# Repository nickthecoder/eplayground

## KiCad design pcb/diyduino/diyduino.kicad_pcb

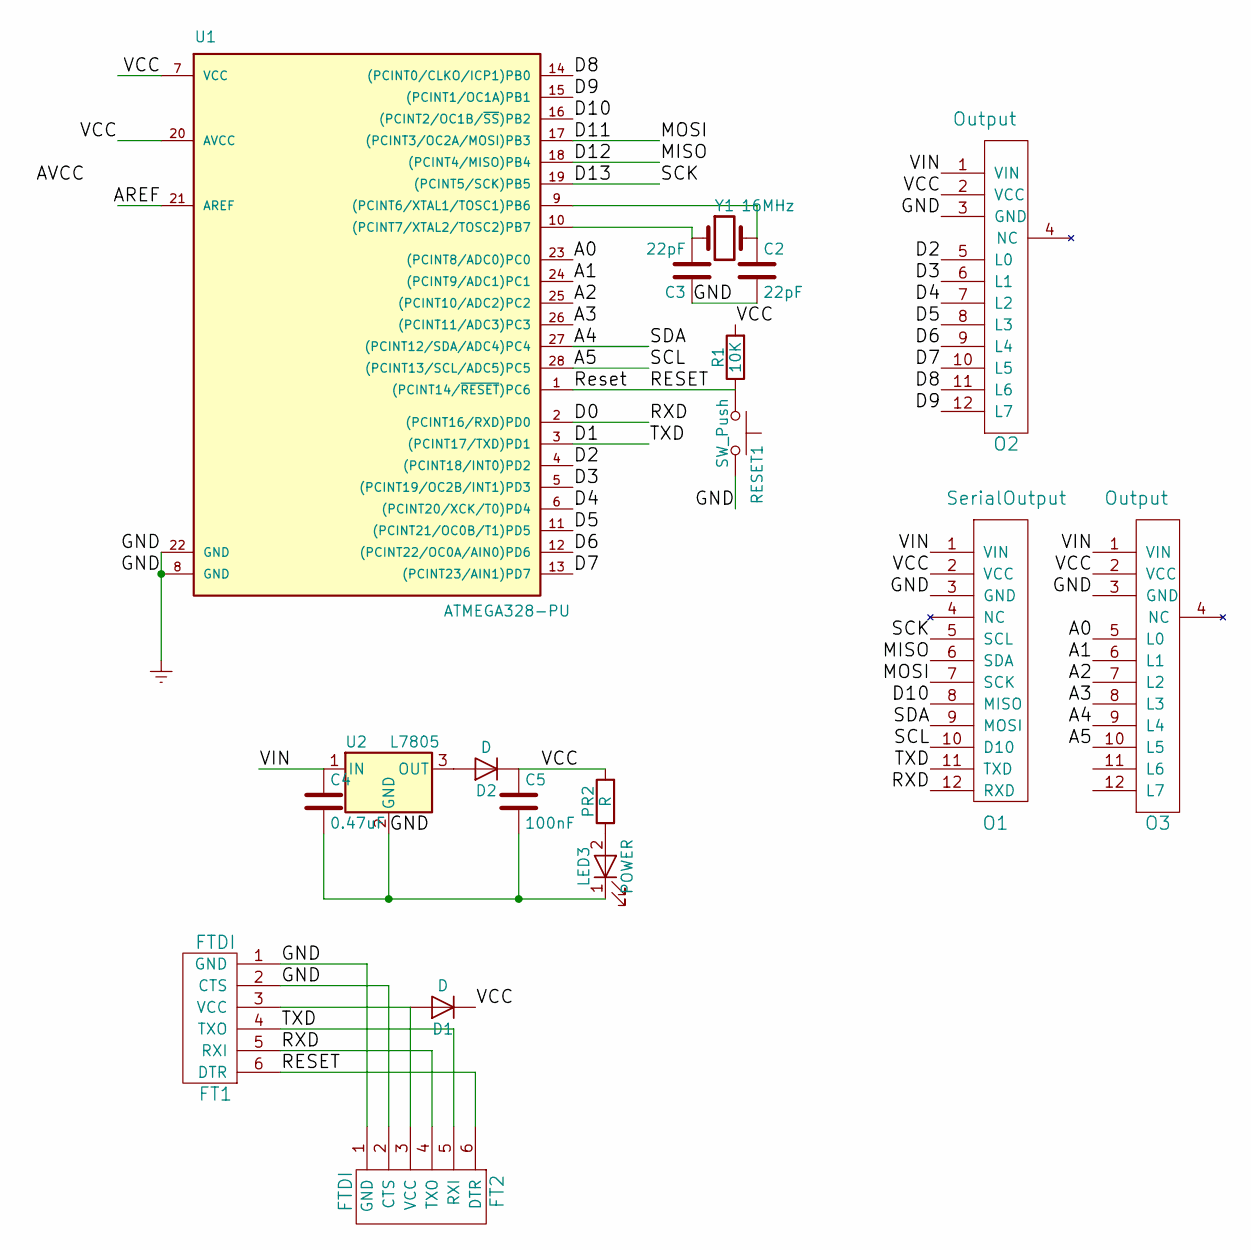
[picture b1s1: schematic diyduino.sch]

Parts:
C2, C3: 22pF; C_Disc_D3.0mm_W1.6mm_P2.50mm
C4: 0.47uF; CP_Radial_D6.3mm_P2.50mm
C5: 100nF; CP_Radial_D6.3mm_P2.50mm
D1, D2: D; D_T-1_P5.08mm_Horizontal
FT1, FT2: FTDI; Pin_Header_Straight_1x06_Pitch2.54mm
LED3: POWER; LED_Rectangular_W3.0mm_H2.0mm
O1: SerialOutput; Socket_Strip_Straight_1x12_Pitch2.54mm
O2, O3: Output; Socket_Strip_Straight_1x12_Pitch2.54mm
PR2: R; R_Axial_DIN0204_L3.6mm_D1.6mm_P7.62mm_Horizontal
R1: 10K; R_Axial_DIN0204_L3.6mm_D1.6mm_P7.62mm_Horizontal
RESET1: SW_Push; SW_PUSH_6mm
U1: ATMEGA328-PU; DIP-28_W7.62mm
U2: L7805; TO-220
Y1: 16MHz; Resonator-2pin_w6.0mm_h3.0mm

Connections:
/A0: O3.5 (L0), U1.23 ((PCINT8/ADC0)PC0)
/A1: O3.6 (L1), U1.24 ((PCINT9/ADC1)PC1)
/A2: O3.7 (L2), U1.25 ((PCINT10/ADC2)PC2)
/A3: O3.8 (L3), U1.26 ((PCINT11/ADC3)PC3)
/A4: O1.9 (MOSI), O3.9 (L4), U1.27 ((PCINT12/SDA/ADC4)PC4)
/A5: O1.10 (D10), O3.10 (L5), U1.28 ((PCINT13/SCL/ADC5)PC5)
/D0: FT1.5 (RXI), FT2.4 (TXO), O1.12 (RXD), U1.2 ((PCINT16/RXD)PD0)
/D1: FT1.4 (TXO), FT2.5 (RXI), O1.11 (TXD), U1.3 ((PCINT17/TXD)PD1)
/D2: O2.5 (L0), U1.4 ((PCINT18/INT0)PD2)
/D3: O2.6 (L1), U1.5 ((PCINT19/OC2B/INT1)PD3)
/D4: O2.7 (L2), U1.6 ((PCINT20/XCK/T0)PD4)
/D5: O2.8 (L3), U1.11 ((PCINT21/OC0B/T1)PD5)
/D6: O2.9 (L4), U1.12 ((PCINT22/OC0A/AIN0)PD6)
/D7: O2.10 (L5), U1.13 ((PCINT23/AIN1)PD7)
/D8: O2.11 (L6), U1.14 ((PCINT0/CLKO/ICP1)PB0)
/D9: O2.12 (L7), U1.15 ((PCINT1/OC1A)PB1)
/D10: O1.8 (MISO), U1.16 ((PCINT2/OC1B/~SS~)PB2)
/D11: O1.7 (SCK), U1.17 ((PCINT3/OC2A/MOSI)PB3)
/D12: O1.6 (SDA), U1.18 ((PCINT4/MISO)PB4)
/D13: O1.5 (SCL), U1.19 ((PCINT5/SCK)PB5)
/RESET: FT1.6 (DTR), FT2.6 (DTR), R1.1, RESET1.1, U1.1 ((PCINT14/~RESET~)PC6)
/VCC: C5.1, D1.1 (K), D2.1 (K), O1.2 (VCC), O2.2 (VCC), O3.2 (VCC), PR2.2, R1.2, U1.7 (VCC), U1.20 (AVCC)
/VIN: C4.1, O1.1 (VIN), O2.1 (VIN), O3.1 (VIN), U2.1 (IN)
Earth: C2.2, C3.1, C4.2, C5.2, FT1.1 (GND), FT1.2 (CTS), FT2.1 (GND), FT2.2 (CTS), LED3.1 (K), O1.3 (GND), O2.3 (GND), O3.3 (GND), RESET1.2, U1.8 (GND), U1.22 (GND), U2.2 (GND)
unnamed: C2.1, U1.9 ((PCINT6/XTAL1/TOSC1)PB6), Y1.2
unnamed: C3.2, U1.10 ((PCINT7/XTAL2/TOSC2)PB7), Y1.1
unnamed: D1.2 (A), FT1.3 (VCC), FT2.3 (VCC)
unnamed: D2.2 (A), U2.3 (OUT)
unnamed: LED3.2 (A), PR2.1

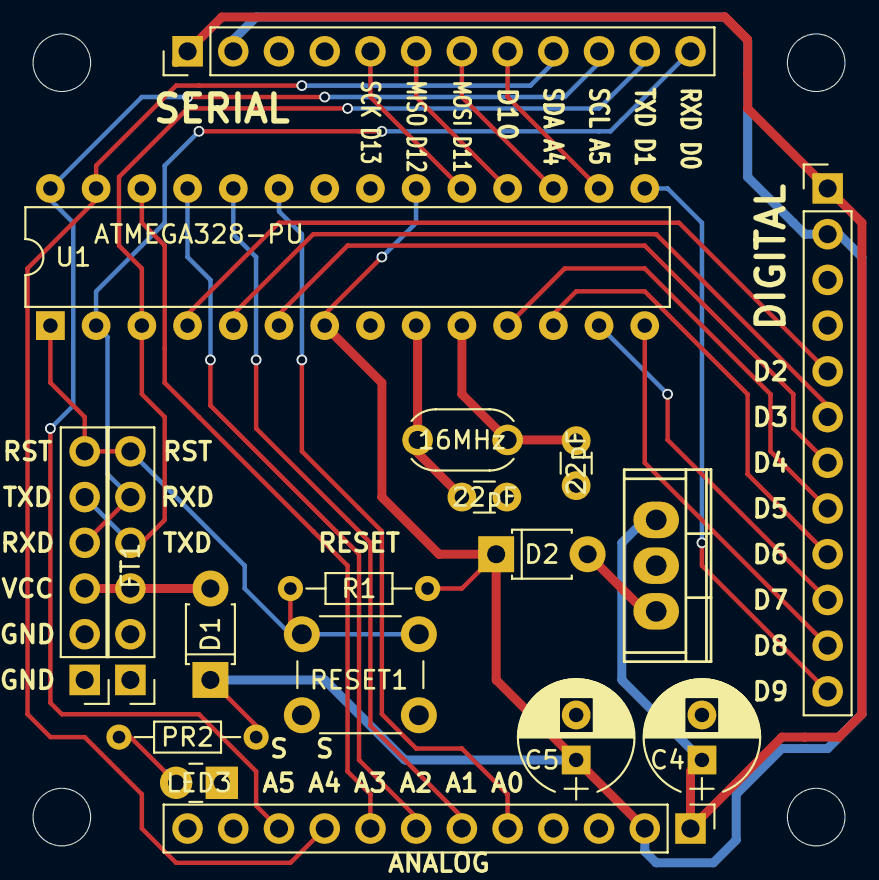
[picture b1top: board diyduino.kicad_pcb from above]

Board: 2 copper layers, 20 parts (0 on the bottom side), 29 nets.

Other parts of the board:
X: M3; MountingHole_3.2mm_M3
X#2: M3; MountingHole_3.2mm_M3

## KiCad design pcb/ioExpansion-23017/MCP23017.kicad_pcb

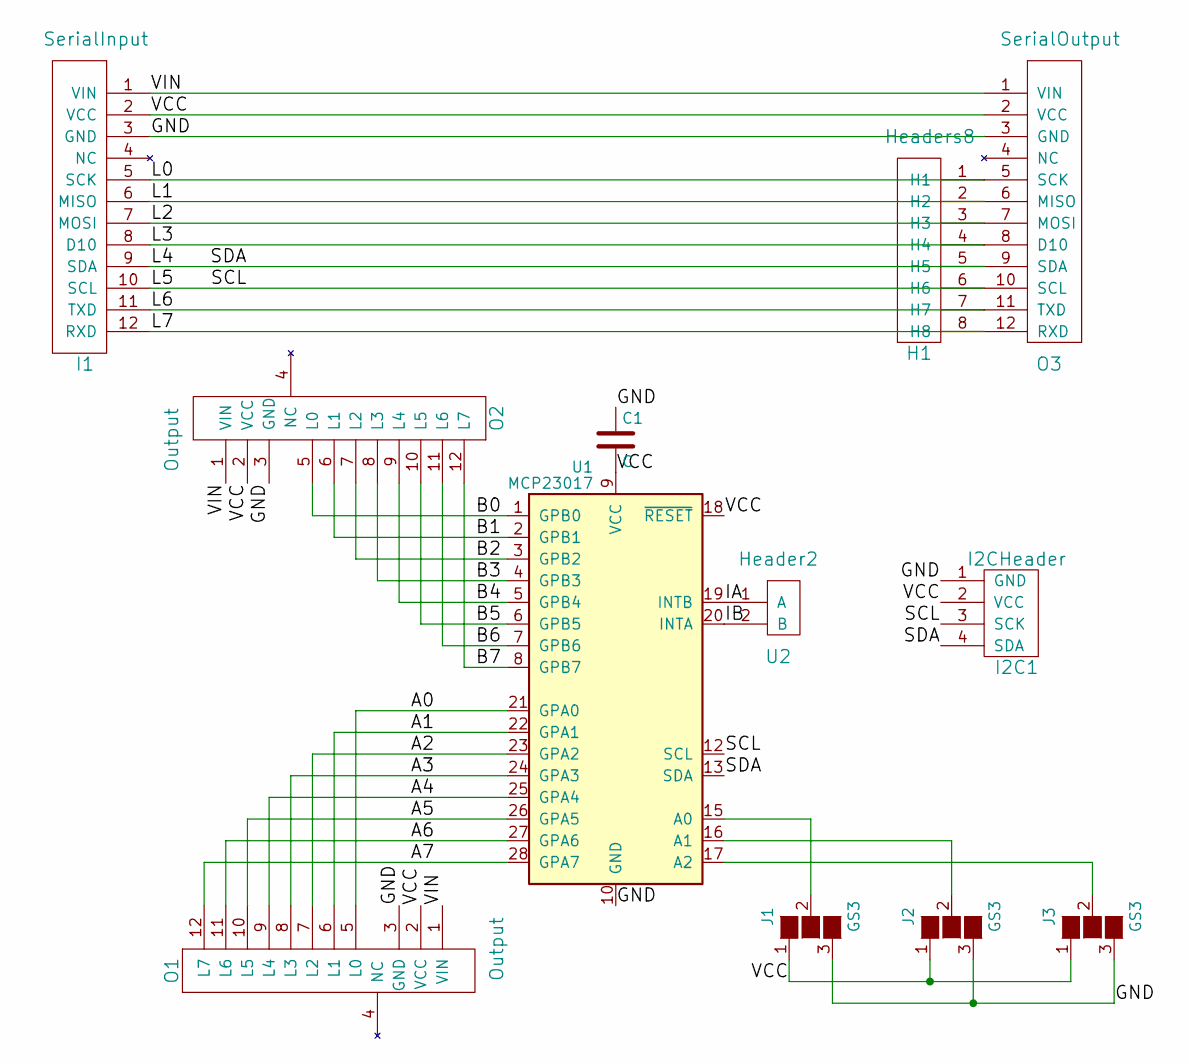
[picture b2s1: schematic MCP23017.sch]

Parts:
C1: C; C_Disc_D3.8mm_W2.6mm_P2.50mm
H1: Headers8; Pin_Header_Straight_1x08_Pitch2.54mm
I1: SerialInput; Socket_Strip_Straight_1x12_Pitch2.54mm
I2C1: I2CHeader; Pin_Header_Straight_1x04_Pitch2.54mm
J1, J2, J3: GS3
O1, O2: Output; Socket_Strip_Straight_1x12_Pitch2.54mm
O3: SerialOutput; Socket_Strip_Straight_1x12_Pitch2.54mm
U1: MCP23017; DIP-28_W7.62mm
U2: Header2; Pin_Header_Straight_1x02_Pitch2.54mm

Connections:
/A0: O1.5 (L0), U1.21 (GPA0)
/A1: O1.6 (L1), U1.22 (GPA1)
/A2: O1.7 (L2), U1.23 (GPA2)
/A3: O1.8 (L3), U1.24 (GPA3)
/A4: O1.9 (L4), U1.25 (GPA4)
/A5: O1.10 (L5), U1.26 (GPA5)
/A6: O1.11 (L6), U1.27 (GPA6)
/A7: O1.12 (L7), U1.28 (GPA7)
/B0: O2.5 (L0), U1.1 (GPB0)
/B1: O2.6 (L1), U1.2 (GPB1)
/B2: O2.7 (L2), U1.3 (GPB2)
/B3: O2.8 (L3), U1.4 (GPB3)
/B4: O2.9 (L4), U1.5 (GPB4)
/B5: O2.10 (L5), U1.6 (GPB5)
/B6: O2.11 (L6), U1.7 (GPB6)
/B7: O2.12 (L7), U1.8 (GPB7)
/GND: C1.1, I1.3 (GND), I2C1.1 (GND), J1.3 (G3), J2.3 (G3), J3.3 (G3), O1.3 (GND), O2.3 (GND), O3.3 (GND), U1.10 (GND)
/IA: U1.19 (INTB), U2.1 (A)
/IB: U1.20 (INTA), U2.2 (B)
/L0: H1.1 (H1), I1.5 (SCK), O3.5 (SCK)
/L1: H1.2 (H2), I1.6 (MISO), O3.6 (MISO)
/L2: H1.3 (H3), I1.7 (MOSI), O3.7 (MOSI)
/L3: H1.4 (H4), I1.8 (D10), O3.8 (D10)
/L4: H1.5 (H5), I1.9 (SDA), I2C1.4 (SDA), O3.9 (SDA), U1.13 (SDA)
/L5: H1.6 (H6), I1.10 (SCL), I2C1.3 (SCK), O3.10 (SCL), U1.12 (SCL)
/L6: H1.7 (H7), I1.11 (TXD), O3.11 (TXD)
/L7: H1.8 (H8), I1.12 (RXD), O3.12 (RXD)
/VCC: C1.2, I1.2 (VCC), I2C1.2 (VCC), J1.1 (G1), J2.1 (G1), J3.1 (G1), O1.2 (VCC), O2.2 (VCC), O3.2 (VCC), U1.9 (VCC), U1.18 (~RESET)
/VIN: I1.1 (VIN), O1.1 (VIN), O2.1 (VIN), O3.1 (VIN)
unnamed: J1.2 (G2), U1.15 (A0)
unnamed: J2.2 (G2), U1.16 (A1)
unnamed: J3.2 (G2), U1.17 (A2)

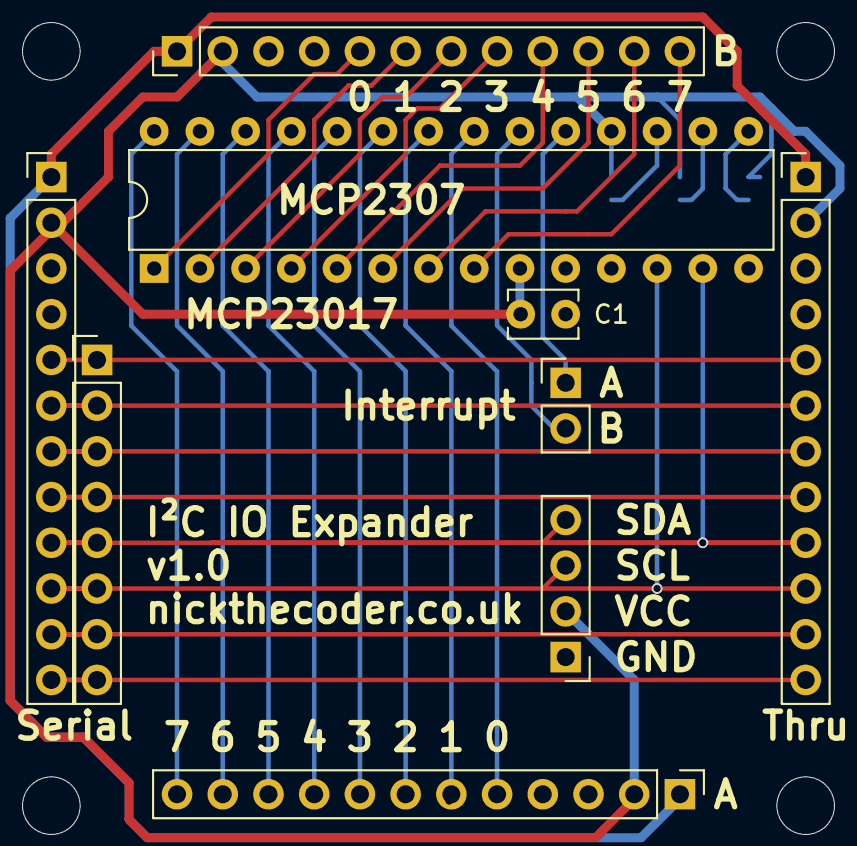
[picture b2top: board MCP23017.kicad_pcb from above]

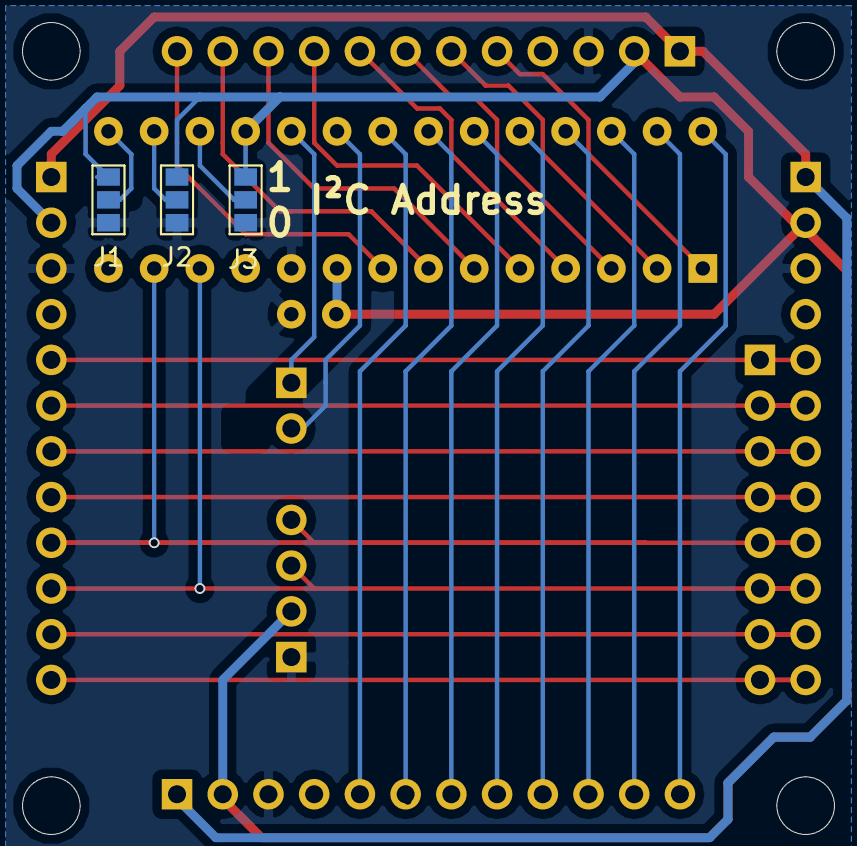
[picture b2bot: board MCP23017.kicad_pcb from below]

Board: 2 copper layers, 14 parts (3 on the bottom side), 32 nets.

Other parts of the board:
M3, M3#2: MountingHole_3.2mm_M3

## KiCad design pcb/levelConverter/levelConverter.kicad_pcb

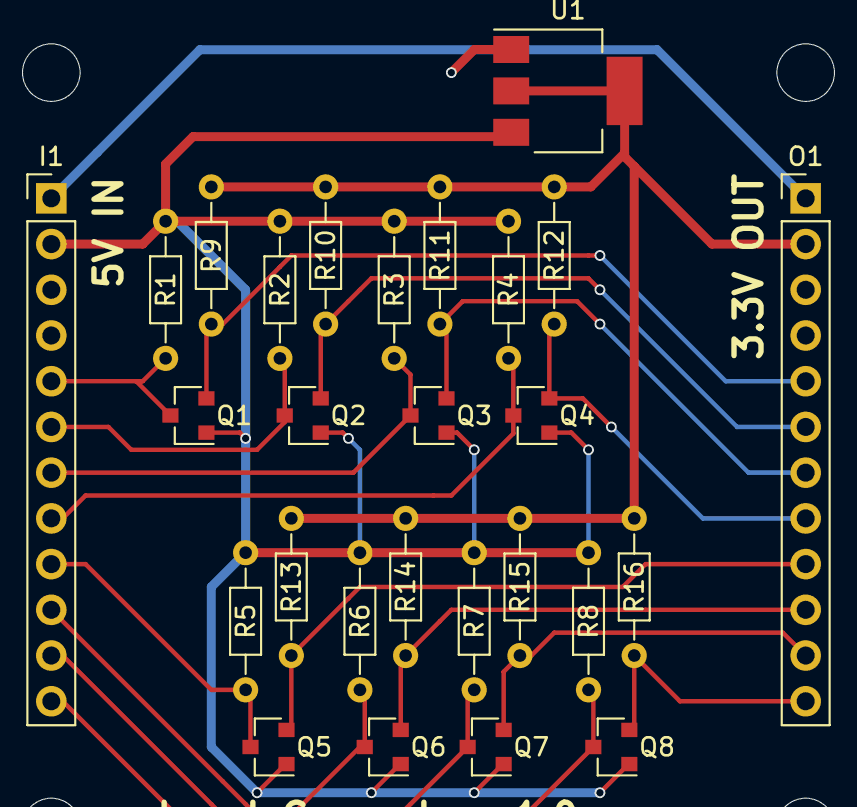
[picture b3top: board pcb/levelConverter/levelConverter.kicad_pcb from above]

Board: 2 copper layers, 29 parts (0 on the bottom side), 20 nets.

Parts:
I1: Input; Pin_Header_Straight_1x12_Pitch2.54mm
M3, M3#2: MountingHole_3.2mm_M3
O1: Output; Socket_Strip_Straight_1x12_Pitch2.54mm
Q1, Q2, Q3, Q4, Q5, Q6, Q7, Q8: BSS138; SOT-23
R1, R2, R3, R4, R5, R6, R7, R8, R9, R10, R11, R12, R13, R14, R15, R16: R; R_Axial_DIN0204_L3.6mm_D1.6mm_P7.62mm_Horizontal
U1: AP1117-33; SOT-223-3Lead_TabPin2

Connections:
/3v3: O1.2, R9.1, R10.1, R11.1, R12.1, R13.1, R14.1, R15.1, R16.1, U1.2
/5V: I1.2, Q1.1, Q2.1, Q3.1, Q4.1, Q5.1, Q6.1, Q7.1, Q8.1, R1.2, R2.1, R3.1, R4.1, R5.1, R6.1, R7.1, R8.1, U1.3
/L0: I1.5, Q1.3, R1.1
/L1: I1.6, Q2.3, R2.2
/L2: I1.7, Q3.3, R3.2
/L3: I1.8, Q4.3, R4.2
/L4: I1.9, Q5.3, R5.2
/L5: I1.10, Q6.3, R6.2
/L6: I1.11, Q7.3, R7.2
/L7: I1.12, Q8.3, R8.2
/VIN: I1.1, O1.1
Earth: I1.3, O1.3, U1.1
unnamed: O1.5, Q1.2, R9.2
unnamed: O1.6, Q2.2, R10.2
unnamed: O1.7, Q3.2, R11.2
unnamed: O1.8, Q4.2, R12.2
unnamed: O1.9, Q5.2, R13.2
unnamed: O1.10, Q6.2, R14.2
unnamed: O1.11, Q7.2, R15.2
unnamed: O1.12, Q8.2, R16.2

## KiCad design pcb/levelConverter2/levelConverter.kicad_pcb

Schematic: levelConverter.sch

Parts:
H1: Data; Pin_Header_Straight_1x08_Pitch2.54mm
H2: GND; Pin_Header_Straight_1x08_Pitch2.54mm
H3: VCC; Pin_Header_Straight_1x08_Pitch2.54mm
I1, I2: Input; Pin_Header_Straight_1x12_Pitch2.54mm
J1, J3: S; Pin_Header_Straight_1x01_Pitch2.54mm
J2, J4: Term; TerminalBlock_Pheonix_MPT-2.54mm_3pol
O1, O2: Output; Socket_Strip_Straight_1x12_Pitch2.54mm
Q1, Q2, Q3, Q4, Q5, Q6, Q7, Q8: BSS138; SOT-23
RN1, RN2: R_Network08; R_Array_SIP9
U1: AP1117-33; SOT-223-3Lead_TabPin2

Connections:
/3v3: O1.2 (VCC), RN1.1 (common), U1.2 (VO)
/5V: I1.2 (VCC), Q1.1 (G), Q2.1 (G), Q3.1 (G), Q4.1 (G), Q5.1 (G), Q6.1 (G), Q7.1 (G), Q8.1 (G), RN2.1 (common), U1.3 (VI)
/L0: I1.5 (L0), Q1.3 (D), RN2.2 (R1)
/L1: I1.6 (L1), Q2.3 (D), RN2.3 (R2)
/L2: I1.7 (L2), Q3.3 (D), RN2.4 (R3)
/L3: I1.8 (L3), Q4.3 (D), RN2.5 (R4)
/L4: I1.9 (L4), Q5.3 (D), RN2.6 (R5)
/L5: I1.10 (L5), Q6.3 (D), RN2.7 (R6)
/L6: I1.11 (L6), Q7.3 (D), RN2.8 (R7)
/L7: I1.12 (L7), Q8.3 (D), RN2.9 (R8)
/VIN: I1.1 (VIN), O1.1 (VIN)
Earth: H2.1 (H1), H2.2 (H2), H2.3 (H3), H2.4 (H4), H2.5 (H5), H2.6 (H6), H2.7 (H7), H2.8 (H8), I1.3 (GND), I2.3 (GND), J2.1, J4.1, O1.3 (GND), O2.3 (GND), U1.1 (GND)
unnamed: H1.1 (H1), I2.5 (L0), O2.5 (L0)
unnamed: H1.2 (H2), I2.6 (L1), O2.6 (L1)
unnamed: H1.3 (H3), I2.7 (L2), O2.7 (L2)
unnamed: H1.4 (H4), I2.8 (L3), O2.8 (L3)
unnamed: H1.5 (H5), I2.9 (L4), O2.9 (L4)
unnamed: H1.6 (H6), I2.10 (L5), O2.10 (L5)
unnamed: H1.7 (H7), I2.11 (L6), O2.11 (L6)
unnamed: H1.8 (H8), I2.12 (L7), O2.12 (L7)
unnamed: H3.1 (H1), H3.2 (H2), H3.3 (H3), H3.4 (H4), H3.5 (H5), H3.6 (H6), H3.7 (H7), H3.8 (H8), I2.2 (VCC), J2.2, J4.2, O2.2 (VCC)
unnamed: I2.1 (VIN), O2.1 (VIN)
unnamed: J1.1, J2.3
unnamed: J3.1, J4.3
unnamed: O1.5 (L0), Q1.2 (S), RN1.2 (R1)
unnamed: O1.6 (L1), Q2.2 (S), RN1.3 (R2)
unnamed: O1.7 (L2), Q3.2 (S), RN1.4 (R3)
unnamed: O1.8 (L3), Q4.2 (S), RN1.5 (R4)
unnamed: O1.9 (L4), Q5.2 (S), RN1.6 (R5)
unnamed: O1.10 (L5), Q6.2 (S), RN1.7 (R6)
unnamed: O1.11 (L6), Q7.2 (S), RN1.8 (R7)
unnamed: O1.12 (L7), Q8.2 (S), RN1.9 (R8)

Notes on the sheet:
https://learn.sparkfun.com/tutorials/bi-directional-logic-level-converter-hookup-guide
Level Converer
Triple Header
Option for one triple using screw terminal

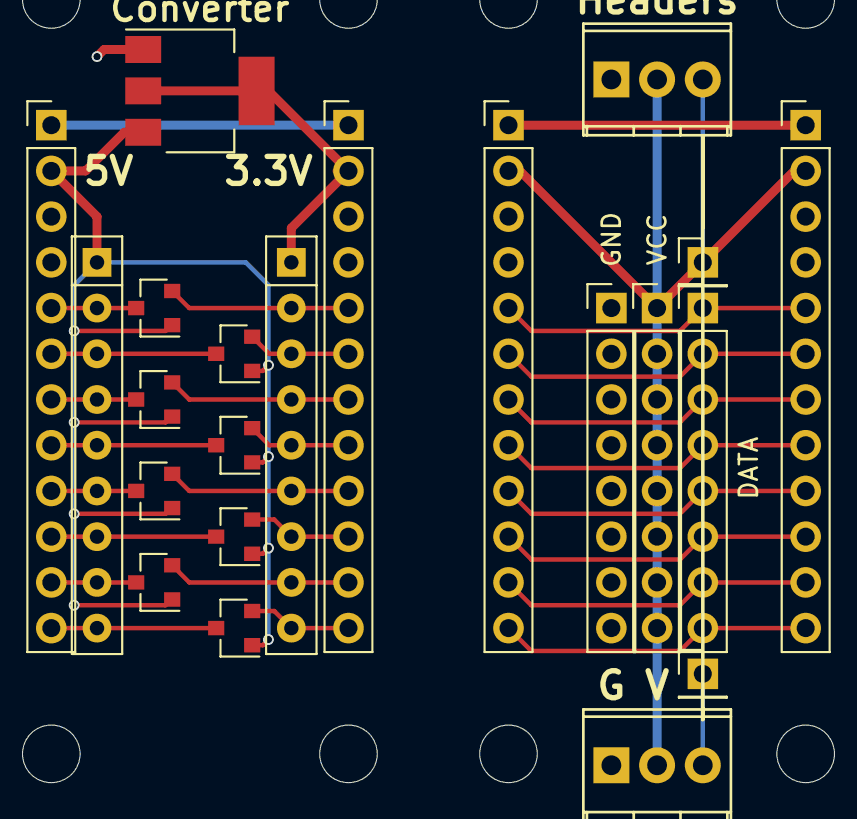
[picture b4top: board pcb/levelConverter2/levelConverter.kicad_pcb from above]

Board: 2 copper layers, 26 parts (0 on the bottom side), 32 nets.

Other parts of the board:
M3, M3#2, M3#3, M3#4: MountingHole_3.2mm_M3

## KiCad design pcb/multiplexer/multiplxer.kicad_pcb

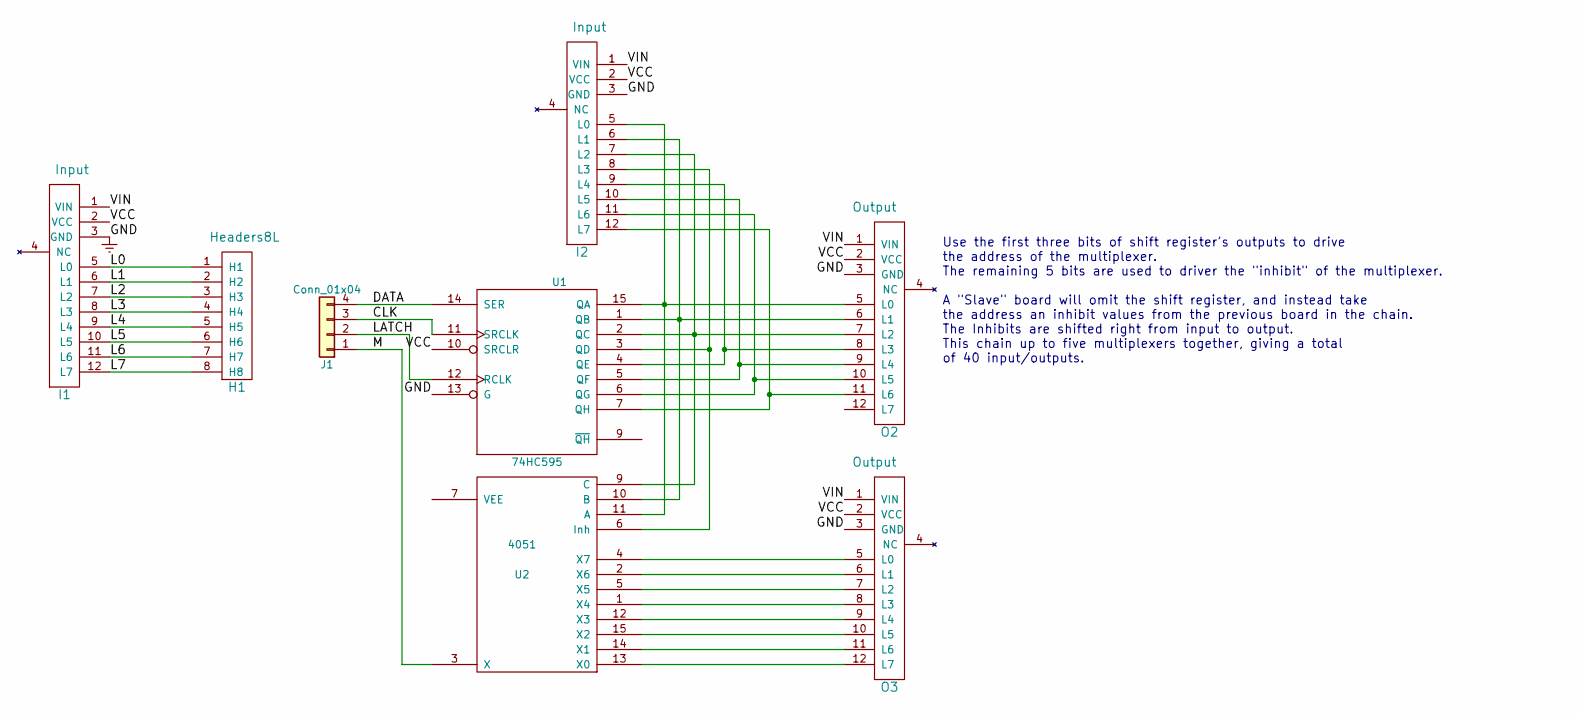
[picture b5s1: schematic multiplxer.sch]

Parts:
H1: Headers8L; Pin_Header_Straight_1x08_Pitch2.54mm
I1, I2: Input; Pin_Header_Straight_1x12_Pitch2.54mm
J1: Conn_01x04; Pin_Header_Straight_1x04_Pitch2.54mm
O2, O3: Output; Socket_Strip_Straight_1x12_Pitch2.54mm
U1: 74HC595; DIP-16_W7.62mm
U2: 4051; DIP-16_W7.62mm

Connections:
/CLK: J1.3, U1.11 (SRCLK)
/DATA: J1.4, U1.14 (SER)
/L0: H1.1 (H1), I1.5 (L0)
/L1: H1.2 (H2), I1.6 (L1)
/L2: H1.3 (H3), I1.7 (L2)
/L3: H1.4 (H4), I1.8 (L3)
/L4: H1.5 (H5), I1.9 (L4)
/L5: H1.6 (H6), I1.10 (L5)
/L6: H1.7 (H7), I1.11 (L6)
/L7: H1.8 (H8), I1.12 (L7)
/LATCH: J1.2, U1.12 (RCLK)
/M: J1.1, U2.3 (X)
/VIN: I1.1 (VIN), I2.1 (VIN), O2.1 (VIN), O3.1 (VIN)
Earth: I1.3 (GND), I2.3 (GND), O2.3 (GND), O3.3 (GND), U1.8 (GND), U1.13 (G)
unnamed: I2.5 (L0), O2.5 (L0), U1.15 (QA), U2.11 (A)
unnamed: I2.6 (L1), O2.6 (L1), U1.1 (QB), U2.10 (B)
unnamed: I2.7 (L2), O2.7 (L2), U1.2 (QC), U2.9 (C)
unnamed: I2.8 (L3), U1.3 (QD), U2.6 (Inh)
unnamed: I2.9 (L4), O2.8 (L3), U1.4 (QE)
unnamed: I2.10 (L5), O2.9 (L4), U1.5 (QF)
unnamed: I2.11 (L6), O2.10 (L5), U1.6 (QG)
unnamed: I2.12 (L7), O2.11 (L6), U1.7 (QH)
unnamed: O3.5 (L0), U2.4 (X7)
unnamed: O3.6 (L1), U2.2 (X6)
unnamed: O3.7 (L2), U2.5 (X5)
unnamed: O3.8 (L3), U2.1 (X4)
unnamed: O3.9 (L4), U2.12 (X3)
unnamed: O3.10 (L5), U2.15 (X2)
unnamed: O3.11 (L6), U2.14 (X1)
unnamed: O3.12 (L7), U2.13 (X0)
VCC: I1.2 (VCC), I2.2 (VCC), O2.2 (VCC), O3.2 (VCC), U1.10 (SRCLR), U1.16 (VCC)

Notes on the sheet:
Use the first three bits of shift register's outputs to drive the address of the multiplexer. The remaining 5 bits are used to driver the "inhibit" of the multiplexer. A "Slave" board will omit the shift register, and instead take the address an inhibit values from the previous board in the chain. 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

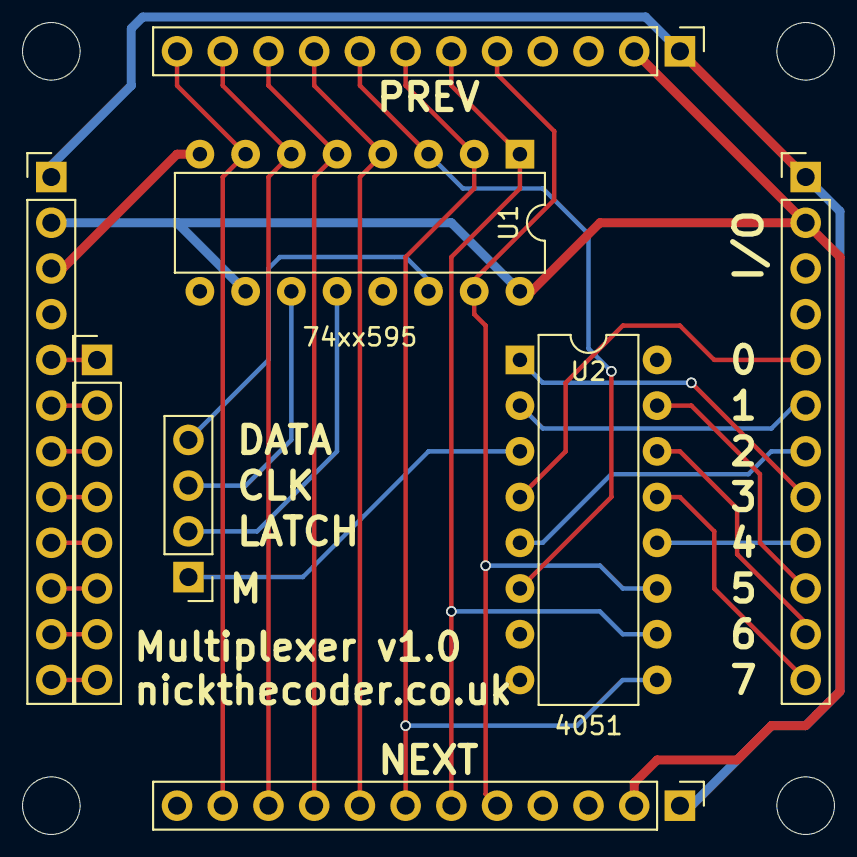
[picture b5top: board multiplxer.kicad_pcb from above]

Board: 2 copper layers, 10 parts (0 on the bottom side), 31 nets.

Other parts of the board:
M3, M3#2: MountingHole_3.2mm_M3

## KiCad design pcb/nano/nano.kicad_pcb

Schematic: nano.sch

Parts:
J2: Header2; Pin_Header_Straight_1x15_Pitch2.54mm
J3: Header1; Pin_Header_Straight_1x15_Pitch2.54mm
O1: SerialOutput; Socket_Strip_Straight_1x12_Pitch2.54mm
O2, O3: Output; Socket_Strip_Straight_1x12_Pitch2.54mm
XA1: Arduino_Nano_Socket; Arduino_Nano

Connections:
/3V3: J2.14, XA1.3V3 (3.3V)
/A0: J2.12, O3.12 (L7), XA1.A0
/A1: J2.11, O3.11 (L6), XA1.A1
/A2: J2.10, O3.10 (L5), XA1.A2
/A3: J2.9, O3.9 (L4), XA1.A3
/A4: J2.8, O1.9 (SDA), O3.8 (L3), XA1.A4 (A4_SDA)
/A5: J2.7, O1.10 (SCL), O3.7 (L2), XA1.A5 (A5_SCL)
/A6: J2.6, O3.6 (L1), XA1.A6
/A7: J2.5, O3.5 (L0), XA1.A7
/AREF: J2.13, XA1.AREF
/D0: J3.2, O1.12 (RXD), XA1.D0 (D0_RX0)
/D1: J3.1, O1.11 (TXD), XA1.D1 (D1_TX0)
/D2: J3.5, O2.5 (L0), XA1.D2 (D2_INT0)
/D3: J3.6, O2.6 (L1), XA1.D3 (D3_INT1)
/D4: J3.7, O2.7 (L2), XA1.D4
/D5: J3.8, O2.8 (L3), XA1.D5
/D6: J3.9, O2.9 (L4), XA1.D6
/D7: J3.10, O2.10 (L5), XA1.D7
/D8: J3.11, O2.11 (L6), XA1.D8
/D9: J3.12, O2.12 (L7), XA1.D9
/D10: J3.13, O1.8 (D10), XA1.D10 (D10_CS)
/D11: J3.14, O1.7 (MOSI), XA1.D11 (D11_MOSI)
/D12: J3.15, O1.6 (MISO), XA1.D12 (D12_MISO)
/D13: J2.15, O1.5 (SCK), XA1.D13 (D13_SCK)
/GND: J2.2, J3.4, O1.3 (GND), O2.3 (GND), O3.3 (GND), XA1.GND1 (GND), XA1.GND2 (GND)
/Reset1: J3.3, XA1.RST1 (RESET)
/Reset2: J2.3, XA1.RST2 (RESET)
/VCC: J2.4, O1.2 (VCC), O2.2 (VCC), O3.2 (VCC), XA1.5V
/VIN: J2.1, O1.1 (VIN), O2.1 (VIN), O3.1 (VIN), XA1.VIN

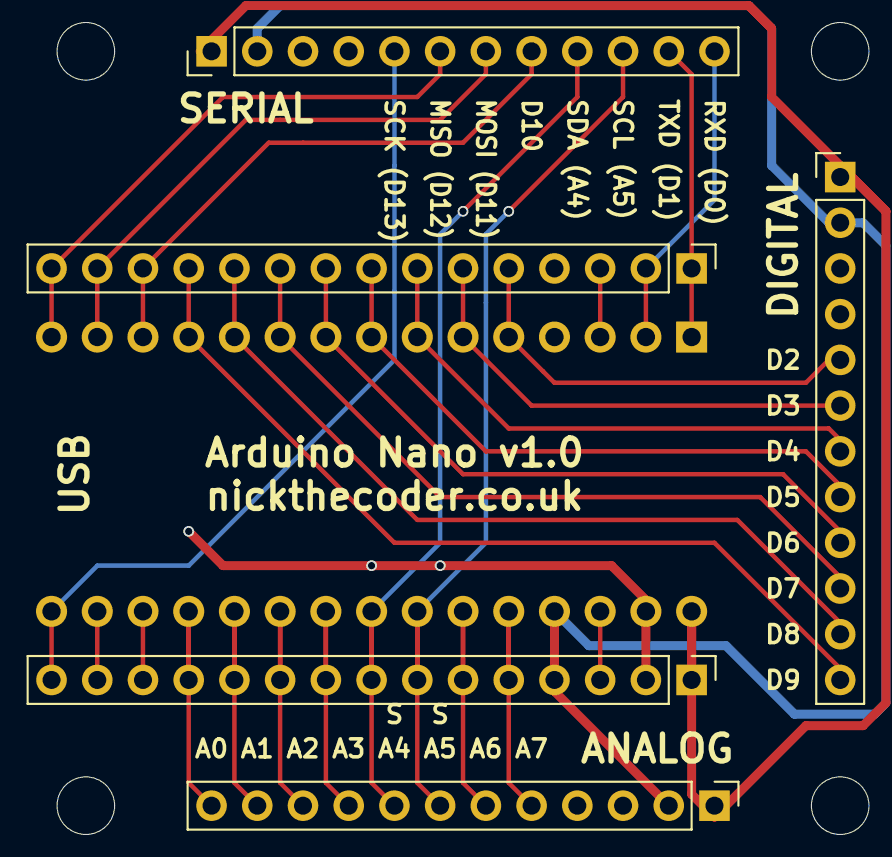
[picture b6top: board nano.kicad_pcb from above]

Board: 2 copper layers, 8 parts (0 on the bottom side), 29 nets.

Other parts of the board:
X: M3; MountingHole_3.2mm_M3
X#2: M3; MountingHole_3.2mm_M3

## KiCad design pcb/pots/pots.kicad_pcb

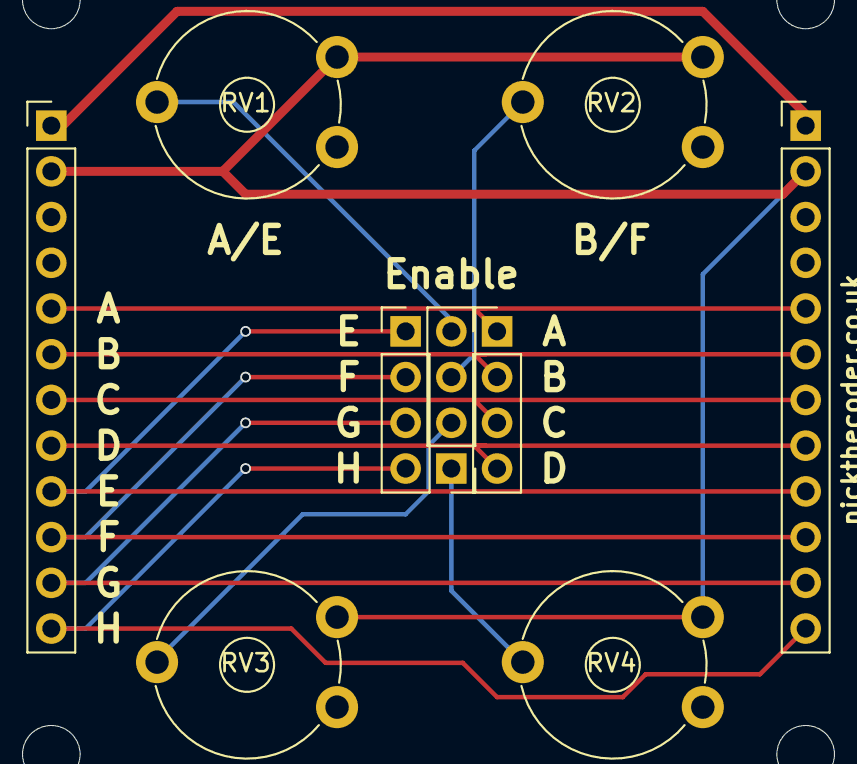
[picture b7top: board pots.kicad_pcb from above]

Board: 2 copper layers, 11 parts (0 on the bottom side), 15 nets.

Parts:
I2: Input; Pin_Header_Straight_1x12_Pitch2.54mm
J1, J2: Choice; Pin_Header_Straight_1x04_Pitch2.54mm
J5: Select; Pin_Header_Straight_1x04_Pitch2.54mm
O2: Output; Socket_Strip_Straight_1x12_Pitch2.54mm
RV1, RV2, RV3, RV4: POT; Potentiometer_Trimmer_Piher_PT-10v10_Horizontal_Px10.0mm_Py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
X: M3; MountingHole_3.2mm_M3
X#2: M3; MountingHole_3.2mm_M3

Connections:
/D0: I2.5, J1.1, O2.5
/D1: I2.6, J1.2, O2.6
/D2: I2.7, J1.3, O2.7
/D3: I2.8, J1.4, O2.8
/D4: I2.9, J2.1, O2.9
/D5: I2.10, J2.2, O2.10
/D6: I2.11, J2.3, O2.11
/D7: I2.12, J2.4, O2.12
/GND2: I2.3, O2.3, RV1.3, RV2.3, RV3.3, RV4.3
/VCC2: I2.2, O2.2, RV1.1, RV2.1, RV3.1, RV4.1
/VIN2: I2.1, O2.1
unnamed: J5.1, RV4.2
unnamed: J5.2, RV3.2
unnamed: J5.3, RV2.2
unnamed: J5.4, RV1.2

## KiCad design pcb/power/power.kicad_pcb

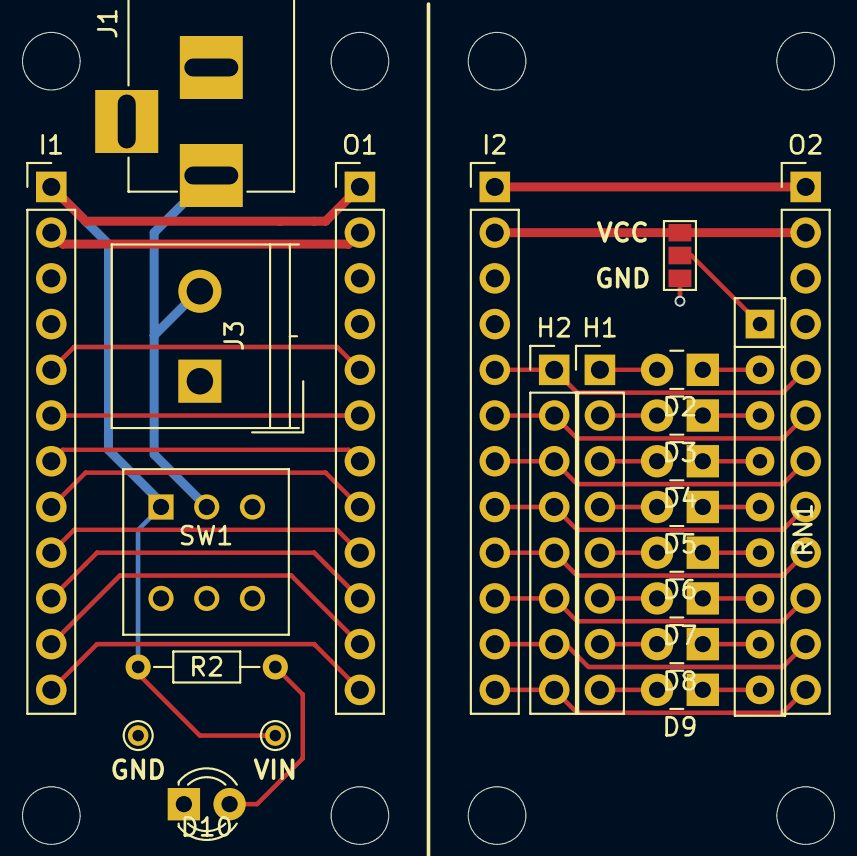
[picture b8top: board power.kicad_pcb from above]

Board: 2 copper layers, 25 parts (0 on the bottom side), 41 nets.

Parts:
D2, D3, D4, D5, D6, D7, D8, D9: LED; LED_Rectangular_W3.0mm_H2.0mm
D10: LED; LED_D3.0mm
H1: Headers8; Pin_Header_Straight_1x08_Pitch2.54mm
H2: Headers8L; Pin_Header_Straight_1x08_Pitch2.54mm
I1, I2: Input; Pin_Header_Straight_1x12_Pitch2.54mm
J1: Conn_Coaxial_Power; BARREL_JACK
J2: GS3
J3: Screw_Terminal_01x02; TerminalBlock_Philmore_TB132_02x5mm_Straight
M3, M3#2: MountingHole_3.2mm_M3
O1, O2: Output; Socket_Strip_Straight_1x12_Pitch2.54mm
R2: R; R_Axial_DIN0204_L3.6mm_D1.6mm_P7.62mm_Horizontal
RN1: R_Network08; R_Array_SIP9
SW1: SW_SPST; SW_SPDT_8mm
TP1, TP2: TEST; PINTST

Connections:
/D0: H2.1, I2.5, O2.5
/D1: H2.2, I2.6, O2.6
/D2: H2.3, I2.7, O2.7
/D3: H2.4, I2.8, O2.8
/D4: H2.5, I2.9, O2.9
/D5: H2.6, I2.10, O2.10
/D6: H2.7, I2.11, O2.11
/D7: H2.8, I2.12, O2.12
/GND2: I2.3, J2.3, O2.3
/L0: I1.5, O1.5
/L1: I1.6, O1.6
/L2: I1.7, O1.7
/L3: I1.8, O1.8
/L4: I1.9, O1.9
/L5: I1.10, O1.10
/L6: I1.11, O1.11
/L7: I1.12, O1.12
/POWER: J1.1, J3.2, SW1.2
/VCC: I1.2, O1.2
/VCC2: I2.2, J2.1, O2.2
/VIN: I1.1, O1.1, R2.1, SW1.1, TP1.1
/VIN2: I2.1, O2.1
Earth: D10.1, I1.3, J1.2, J3.1, O1.3, TP2.1
unnamed: D2.1, RN1.2
unnamed: D2.2, H1.1
unnamed: D3.1, RN1.3
unnamed: D3.2, H1.2
unnamed: D4.1, RN1.4
unnamed: D4.2, H1.3
unnamed: D5.1, RN1.5
unnamed: D5.2, H1.4
unnamed: D6.1, RN1.6
unnamed: D6.2, H1.5
unnamed: D7.1, RN1.7
unnamed: D7.2, H1.6
unnamed: D8.1, RN1.8
unnamed: D8.2, H1.7
unnamed: D9.1, RN1.9
unnamed: D9.2, H1.8
unnamed: D10.2, R2.2
unnamed: J2.2, RN1.1
